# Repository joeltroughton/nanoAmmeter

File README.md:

# nanoAmmeter

nanoAmmeter is a small research device designed to measure the voltage applied to, and the current flowing through biological glucose sensors on the order of 10s to 100s of nanoamps.

As glucose is detected by the sensor, its resistance changes. nanoAmmeter measures the current flow through the sensor for later analysis.

## Function

The nanoAmmeter is inserted between the biosensor's negative electrode and ground. The voltage drop across a 100kOhm resistor is amplified by a gain of 101 by a very low offset opamp (Analog LTC2055, ± 3 μV) and finally read by a 16-bit ADC (TI ADS1115). With a FSR of 4.096V, this gives us a theoretical current resolution of 12.4 pA. 

The voltage applied to the positive side of the biosensor is buffered to the ADC with unity gain for a theoretic voltage resolution of 125 μV.

The ADC is read by a STM32F072 MCU at 128 samples per second where it is fed into a finite impulse response, low pass filter and exported via USB. 

## Acknowledgments
Thanks to https://github.com/pms67 for the FIR circular buffer implementation

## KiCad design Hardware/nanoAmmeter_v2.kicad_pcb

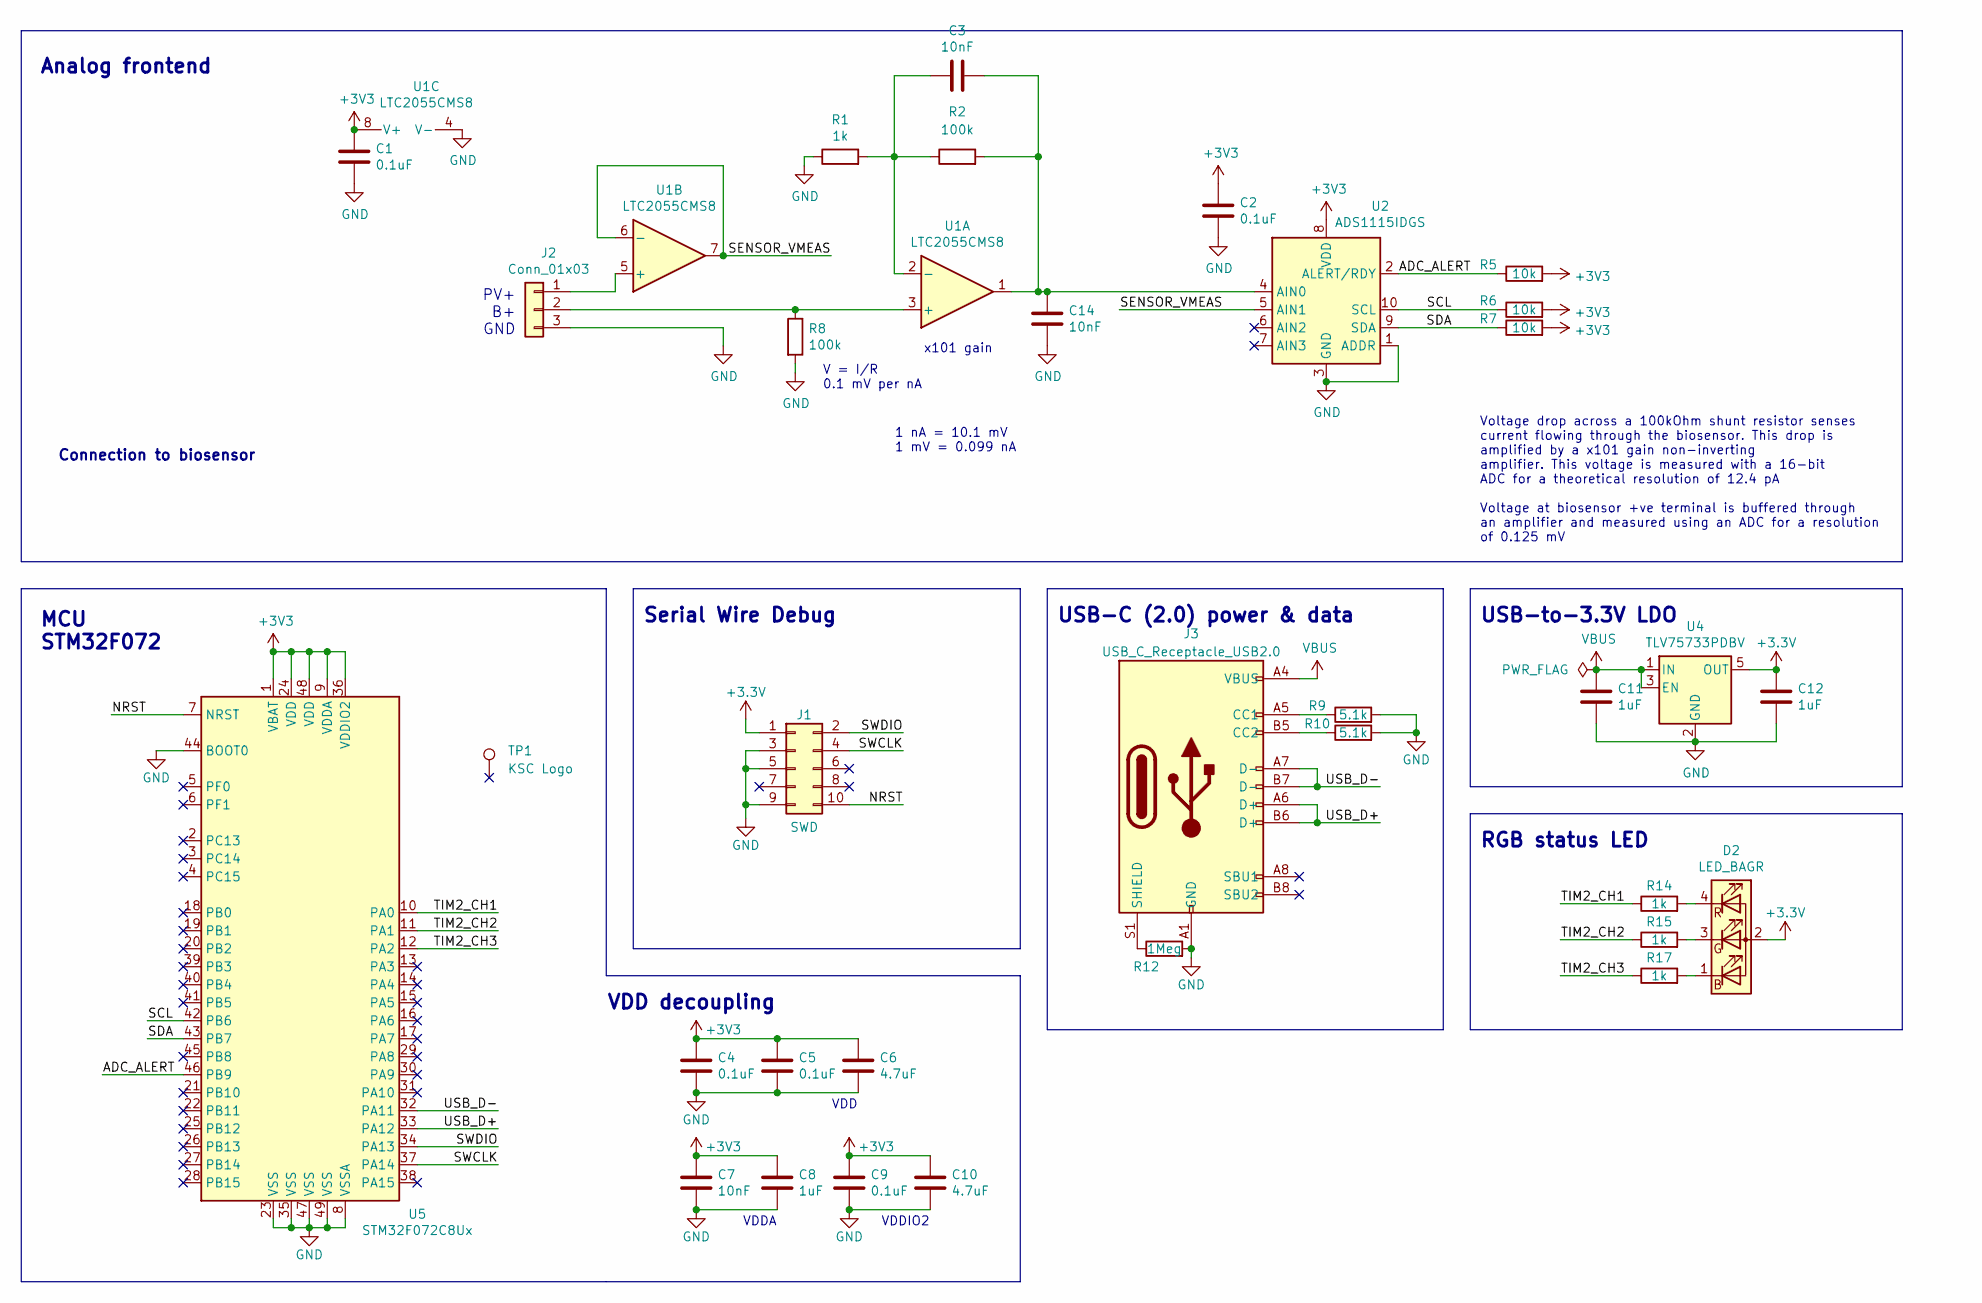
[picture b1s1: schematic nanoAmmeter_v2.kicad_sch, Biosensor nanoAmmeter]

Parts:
C1, C2, C4, C5, C9: 0.1uF; C_0603_1608Metric
C3, C7, C14: 10nF; C_0603_1608Metric
C6, C10: 4.7uF; C_0805_2012Metric
C8, C11, C12: 1uF; C_0603_1608Metric
D2: LED_BAGR; E6C0606RGBC3UDA
J1: SWD; PinHeader_2x05_P1.27mm_Vertical_SMD
J2: Conn_01x03; PinHeader_1x03_P2.54mm_Vertical
J3: USB_C_Receptacle_USB2.0; Molex_105450-0101
R1, R14, R15, R17: 1k; R_0603_1608Metric
R2, R8: 100k; R_0603_1608Metric
R5, R6, R7: 10k; R_0603_1608Metric
R9, R10: 5.1k; R_0603_1608Metric
R12: 1Meg; R_0603_1608Metric
TP1: KSC Logo; ksclogo
U1: LTC2055CMS8; MSOP-8_3x3mm_P0.65mm
U2: ADS1115IDGS; TSSOP-10_3x3mm_P0.5mm
U4: TLV75733PDBV; SOT-23-5
U5: STM32F072C8Ux; QFN-48-1EP_7x7mm_P0.5mm_EP5.6x5.6mm

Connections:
/ADC_ALERT: R5.1, U2.2 (ALERT/RDY), U5.46 (PB9)
/NRST: J1.10, U5.7 (NRST)
/SCL: R6.1, U2.10 (SCL), U5.42 (PB6)
/SDA: R7.1, U2.9 (SDA), U5.43 (PB7)
/SENSOR_VMEAS: U1.6 (-), U1.7, U2.5 (AIN1)
/SWCLK: J1.4, U5.37 (PA14)
/SWDIO: J1.2, U5.34 (PA13)
/TIM2_CH1: R14.1, U5.10 (PA0)
/TIM2_CH2: R15.1, U5.11 (PA1)
/TIM2_CH3: R17.1, U5.12 (PA2)
/USB_D+: J3.A6 (D+), J3.B6 (D+), U5.33 (PA12)
/USB_D-: J3.A7 (D-), J3.B7 (D-), U5.32 (PA11)
GND: C1.2, C2.2, C4.2, C5.2, C6.2, C7.2, C8.2, C9.2, C10.2, C11.2, C12.2, C14.2, J1.3, J1.5, J1.9, J2.3, J3.A1 (GND), J3.A12 (GND), J3.B1 (GND), J3.B12 (GND), R1.1, R8.2, R9.2, R10.2, R12.2, U1.4 (V-), U2.1 (ADDR), U2.3 (GND), U4.2 (GND), U5.8 (VSSA), U5.23 (VSS), U5.35 (VSS), U5.44 (BOOT0), U5.47 (VSS), U5.49 (VSS)
unnamed: C3.1, R1.2, R2.1, U1.2 (-)
unnamed: C3.2, C14.1, R2.2, U1.1, U2.4 (AIN0)
unnamed: D2.1 (BK), R17.2
unnamed: D2.3 (GK), R15.2
unnamed: D2.4 (RK), R14.2
unnamed: J2.1, U1.5 (+)
unnamed: J2.2, R8.1, U1.3 (+)
unnamed: J3.A5 (CC1), R9.1
unnamed: J3.B5 (CC2), R10.1
unnamed: J3.S1 (SHIELD), R12.1
VBUS: C11.1, J3.A4 (VBUS), J3.A9 (VBUS), J3.B4 (VBUS), J3.B9 (VBUS), U4.1 (IN), U4.3 (EN)
no_connect_26: J1.6
no_connect_27: J1.7
no_connect_28: J1.8
no_connect_29: J3.A8 (SBU1)
no_connect_30: J3.B8 (SBU2)
no_connect_32: U2.6 (AIN2)
no_connect_33: U2.7 (AIN3)
no_connect_34: U5.13 (PA3)
no_connect_35: U5.14 (PA4)
no_connect_36: U5.15 (PA5)
no_connect_37: U5.16 (PA6)
no_connect_38: U5.17 (PA7)
no_connect_39: U5.18 (PB0)
no_connect_40: U5.19 (PB1)
no_connect_41: U5.2 (PC13)
no_connect_42: U5.20 (PB2)
no_connect_43: U5.21 (PB10)
no_connect_44: U5.22 (PB11)
no_connect_45: U5.25 (PB12)
no_connect_46: U5.26 (PB13)
no_connect_47: U5.27 (PB14)
no_connect_48: U5.28 (PB15)
no_connect_49: U5.29 (PA8)
no_connect_50: U5.3 (PC14)
no_connect_51: U5.30 (PA9)
no_connect_52: U5.31 (PA10)
no_connect_53: U5.38 (PA15)
no_connect_54: U5.39 (PB3)
no_connect_55: U5.4 (PC15)
no_connect_56: U5.40 (PB4)
no_connect_57: U5.41 (PB5)
no_connect_58: U5.45 (PB8)
no_connect_59: U5.5 (PF0)
no_connect_60: U5.6 (PF1)

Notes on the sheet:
Analog frontend
MCU STM32F072
Connection to biosensor
PV+ B+ GND
VDD decoupling
Serial Wire Debug
VDDA
V = I/R 0.1 mV per nA
VDD
1 nA = 10.1 mV 1 mV = 0.099 nA
VDDIO2
x101 gain
USB-C (2.0) power & data
Voltage drop across a 100kOhm shunt resistor senses current flowing through the biosensor. This drop is amplified by a x101 gain non-inverting amplifier. This voltage is measured with a 16-bit ADC for a theoretical resolution of 12.4 pA Voltage at biosensor +ve terminal is buffered through an ampli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
USB-to-3.3V LDO
RGB status LED

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
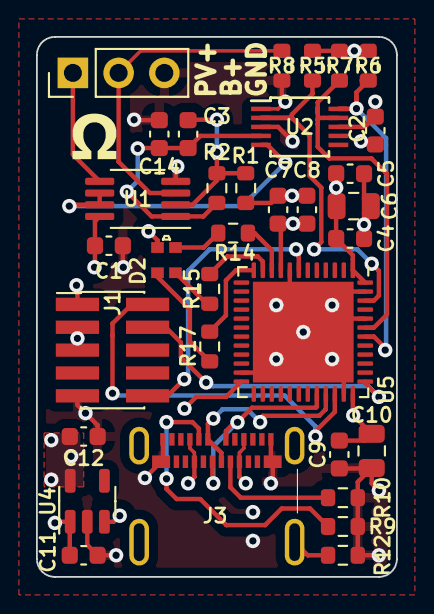
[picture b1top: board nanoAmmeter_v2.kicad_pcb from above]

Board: 4 copper layers, 20.0 x 30.0 mm, 34 parts (1 on the bottom side), 25 nets.

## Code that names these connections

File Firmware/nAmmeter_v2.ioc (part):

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Mcu.Name=STM32F072C(8-B)Ux
Mcu.Package=UFQFPN48
Mcu.UserName=STM32F072C8Ux
PA0.GPIOParameters=GPIO_Label
PA0.GPIO_Label=LED_R
PA0.Signal=GPIO_Output
PA1.GPIOParameters=GPIO_Label
PA1.GPIO_Label=LED_G
PA1.Signal=GPIO_Output
PA11.Mode=Device
PA11.Signal=USB_DM
PA12.Mode=Device
PA12.Signal=USB_DP
PA2.GPIOParameters=GPIO_Label
PA2.GPIO_Label=LED_B
PA2.Signal=GPIO_Output
PB6.Mode=I2C
PB6.Signal=I2C1_SCL
PB7.Mode=I2C
PB7.Signal=I2C1_SDA
PB9.GPIOParameters=GPIO_Label
PB9.GPIO_Label=ADC_Alert
PB9.Signal=GPIO_Input
RCC.SYSCLKFreq_VALUE=48000000
RCC.SYSCLKSource=RCC_SYSCLKSOURCE_HSI48
board=custom

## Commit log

2021-01-25 Added PCB hardware files
2021-01-25 Added image of PCB for readme
2021-01-25 Moved companion application to seperate folder
2021-01-25 Added STM32 firmware code
